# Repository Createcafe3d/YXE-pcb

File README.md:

Big thanks to Rylan @Peachy for opensourcing the entire project.

Peachy Printer was gearing up to manufacture the mini-v1.14 board. If you're wondering what v1.15 is all about, it's a work-in-progress that we started because of a huge panic: right around the time we were getting ready for our final test manufacturing run, the STM32F042 practically vanished from the entire supply chain! We couldn't find them anywhere! So I quickly started redoing the board to use an STM32F070 instead, but in the end the supply chain recovered before we had to pull the trigger on the respin.

**Todos:**
- Create the trans impedence amplifier for the laser sense pin.
  - This lets us tune the laser power to the "draw velocity" - making for nicer cornering and faster printing
  - The sense pin on the laser is currently grounded (and wrongly labeled as "Laser-EN")

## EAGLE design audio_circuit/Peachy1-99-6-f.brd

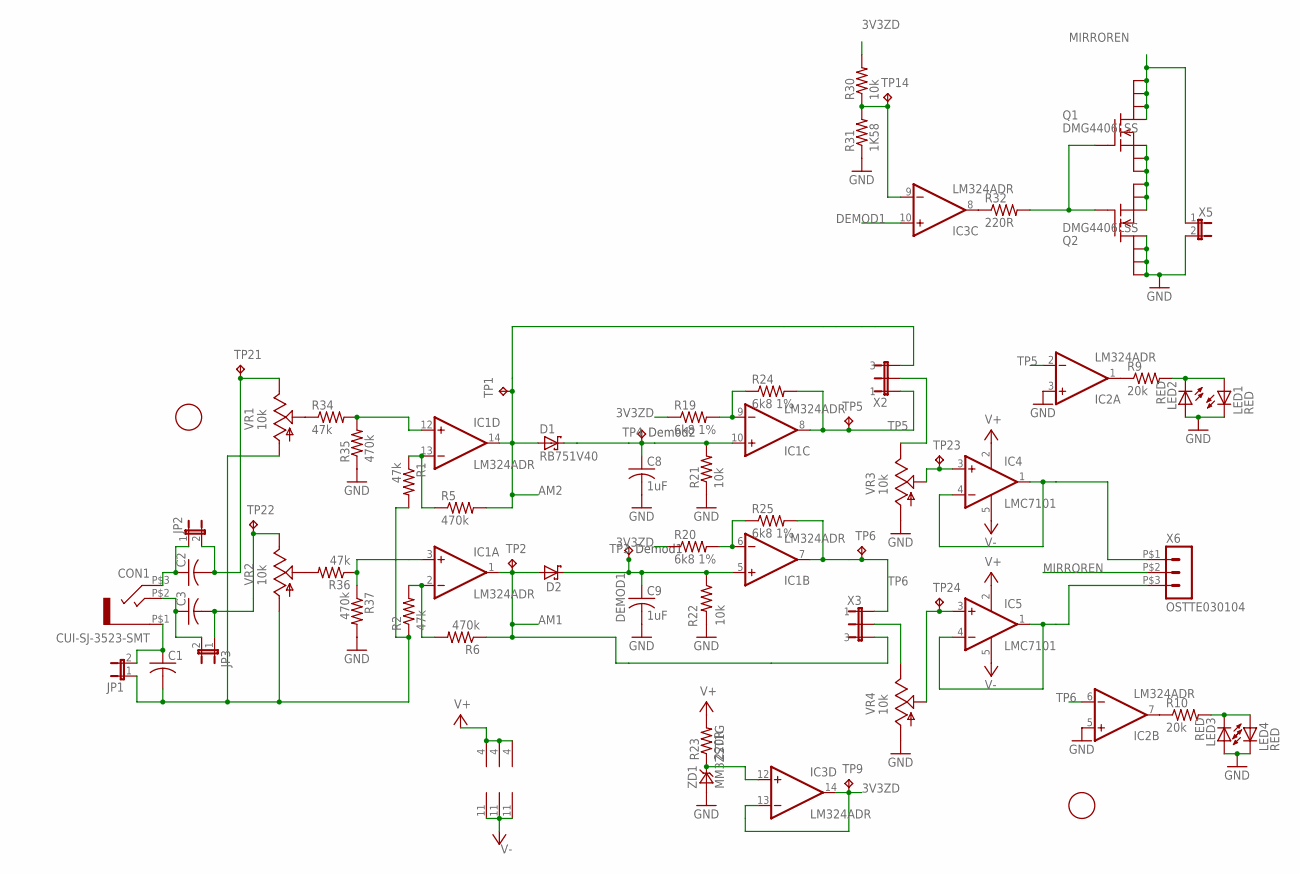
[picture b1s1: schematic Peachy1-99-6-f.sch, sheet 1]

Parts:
C1, C2, C3: C-US0805; C0805
C8, C9: 1uF; C0805; MPN CL21B105KBFNNNE
CON1: CUI-SJ-3523-SMT; MPN SJ-3523-SMT-TR
D1, D2: RB751V40; SOD323-R; MPN RB751V40,115
IC1, IC2, IC3: LM324ADR; SOIC14(TI-PKG-D); MPN LM324ADR
IC4, IC5: LMC7101; SOT23-5; MPN LMC7101BYM5
JP1, JP2, JP3: JUMPER-2SMD-NC; SJ_2S
LED1, LED2, LED3, LED4: RED; CHIPLED_0603; MPN LS L29K-G1J2-1-Z
Q1, Q2: DMG4406LSS; SO8_DMG; MPN DMG4406LSS-13
R1, R2, R34, R36: 47k; R0805; MPN RMCF0805JT47K0; DIGIKEY RMCF0805JT47K0CT-ND
R5, R6, R35, R37: 470k; R0805; MPN RMCF0805JT470K
R9, R10: 20k; R0805; MPN RMCF0805JT20K0
R19, R20, R24, R25: 6k8 1%; R0805; MPN RC0805FR-076K8L
R21, R22, R30: 10k; R0805; MPN RMCF0805JT10K0
R23, R32: 220R; R0805; MPN RMCF0805JT220R
R31: 1K58; R0805; MPN RC0805FR-071K58L
TP1, TP2, TP3, TP4, TP5, TP6, TP9, TP14, TP21, TP22, TP23, TP24: TP017HOLE; TP017TH
U$2, U$3: FIDUCIAL; FIDUCIAL_1MM
VR1, VR2: 10k; 67W; MPN 67WR10KLF
VR3, VR4: 10k; PVZ3A; MPN PVZ3A103C01R00
X2, X3: JUMPER-31-2; SJ_3_PASTE1&2
X5: JUMPER-2SMD-NO; SJ_2S-NO
X6: OSTTE030104; MPN OSTTE030104
ZD1: MM3ZST1G; SOD323-R; MPN BZX384-B3V3,115

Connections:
3V3ZD: IC3.13 (-IN), IC3.14 (OUT), R19.1, R20.1, R30.2, TP9.P$1; also elsewhere on the board
AM1: D2.A, IC1.1 (OUT), R6.1, TP2.P$1, X3.3; also elsewhere on the board
AM2: D1.A, IC1.14 (OUT), R5.2, TP1.P$1, X2.3
DEMOD1: C9.1, D2.C, IC1.5 (+IN), IC3.10 (+IN), R22.1, TP3.P$1
DEMOD2: C8.1, D1.C, IC1.10 (+IN), R21.2, TP4.P$1
GND: C8.2, C9.2, IC2.3 (+IN), IC2.5 (+IN), LED1.C, LED2.A, LED3.A, LED4.C, Q2.P$5 (D), Q2.P$6 (D), Q2.P$7 (D), Q2.P$8 (D), R21.1, R22.2, R31.1, R35.1, R37.2, VR3.P$1 (A), VR4.P$1 (A), X5.2, ZD1.A; also elsewhere on the board
MIRROREN: Q1.P$5 (D), Q1.P$6 (D), Q1.P$7 (D), Q1.P$8 (D), X5.1, X6.P$2 (2)
unnamed: C3.2, JP3.1, TP22.P$1, VR2.E
unnamed: C1.2, JP1.1, R1.2, R2.1, VR1.A, VR2.A
unnamed: R34.1, VR1.S
unnamed: IC1.13 (-IN), R1.1, R5.1
unnamed: IC1.12 (+IN), R34.2, R35.2
unnamed: VR4.P$3 (E), X3.2
unnamed: IC3.12 (+IN), R23.1, ZD1.C
unnamed: IC1.2 (-IN), R2.2, R6.2
unnamed: IC4.3 (+IN), TP23.P$1, VR3.P$2 (S)
unnamed: R36.2, VR2.S
unnamed: IC1.3 (+IN), R36.1, R37.1
unnamed: IC1.9 (-IN), R19.2, R24.1
unnamed: IC2.1 (OUT), R9.1
unnamed: IC1.6 (-IN), R20.2, R25.1
unnamed: IC2.7 (OUT), R10.1
unnamed: IC5.1 (OUT), IC5.4 (-IN), X6.P$3 (3)
unnamed: IC4.1 (OUT), IC4.4 (-IN), X6.P$1 (1)
unnamed: VR3.P$3 (E), X2.2
unnamed: IC5.3 (+IN), TP24.P$1, VR4.P$2 (S)
unnamed: Q1.P$4 (G), Q2.P$4 (G), R32.2
unnamed: Q1.P$1 (S), Q1.P$2 (S), Q1.P$3 (S), Q2.P$1 (S), Q2.P$2 (S), Q2.P$3 (S)
unnamed: IC3.9 (-IN), R30.1, R31.2, TP14.P$1
unnamed: LED1.A, LED2.C, R9.2
unnamed: IC3.8 (OUT), R32.1
unnamed: LED3.C, LED4.A, R10.2
unnamed: C1.1, CON1.P$1 (1), JP1.2
unnamed: C3.1, CON1.P$2 (3), JP3.2
unnamed: C2.1, CON1.P$3 (2), JP2.1
unnamed: C2.2, JP2.2, TP21.P$1, VR1.E
TP5: IC1.8 (OUT), IC2.2 (-IN), R24.2, TP5.P$1, X2.1
TP6: IC1.7 (OUT), IC2.6 (-IN), R25.2, TP6.P$1, X3.1
V+: IC1.4 (V+), IC2.4 (V+), IC3.4 (V+), IC4.2 (V+), IC5.2 (V+), R23.2; also elsewhere on the board
V-: IC1.11 (V-), IC2.11 (V-), IC3.11 (V-), IC4.5 (V-), IC5.5 (V-); also elsewhere on the board

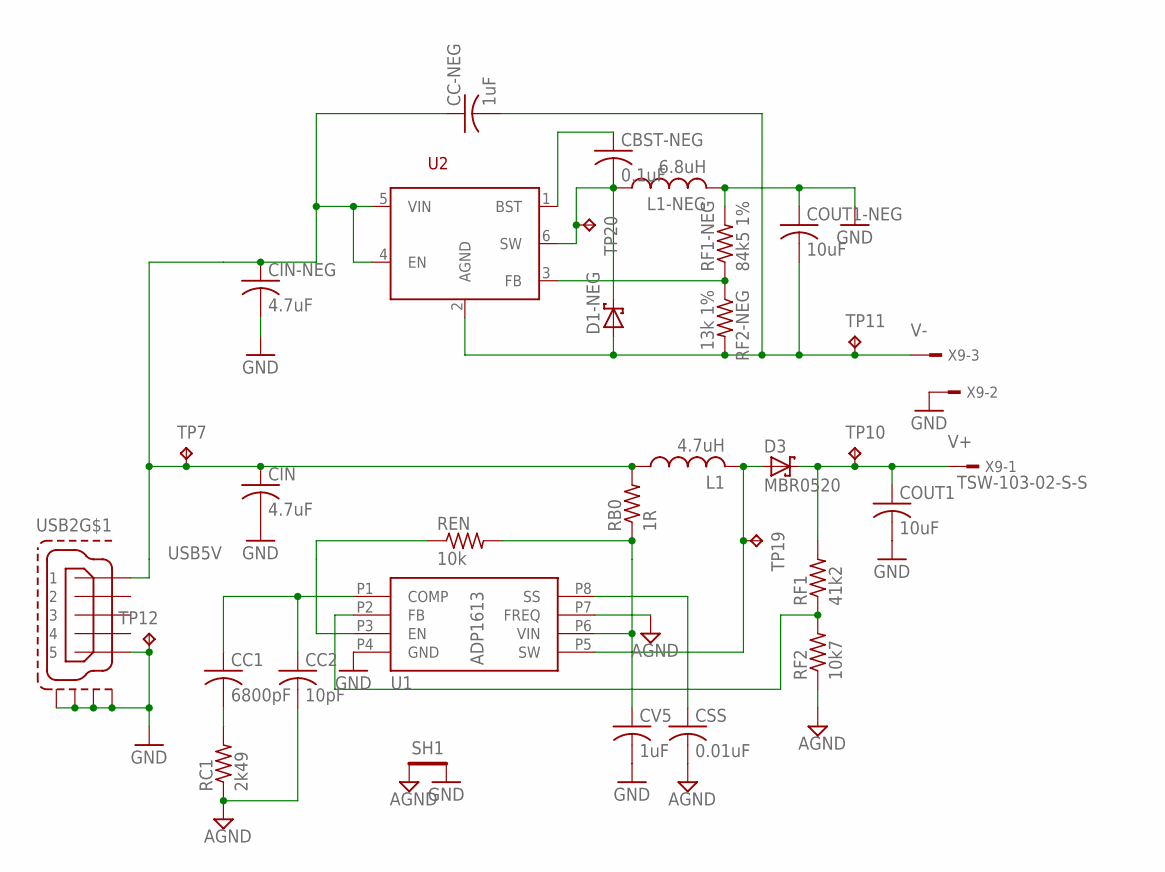
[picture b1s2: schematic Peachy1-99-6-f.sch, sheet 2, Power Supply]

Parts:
CBST-NEG: 0.1uF; C0805; MPN CL21B104KACNNNC
CC1: 6800pF; C0805; MPN CL21B682KBANNNC
CC2: 10pF; C0805; MPN CL21C100JCANNNC
CC-NEG: 1uF; C0805; MPN CL21B105KBFNNNE
CIN: 4.7uF; C0805; MPN CL21A475KOFNNNE
CIN-NEG: 4.7uF; C0805; MPN CL21A475KOFNNNE
COUT1, COUT1-NEG: 10uF; C0805; MPN CL21B106KQQNNNE
CSS: 0.01uF; C0805; MPN CL21B103KBANNNC
CV5: 1uF; C0805; MPN CL21B105KBFNNNE
D1-NEG, D3: MBR0520; SOD123; MPN MBR0520LT3G
L1: 4.7uH; L1210; MPN LQH32PN4R7NN0L
L1-NEG: 6.8uH; L1210; MPN LQH32PN6R8NN0
RB0: 1R; R0805; MPN RMCF0805JT1R00
RC1: 2k49; R0805; MPN RMCF0805FT2K49
REN: 10k; R0805; MPN RMCF0805JT10K0
RF1: 41k2; R0805; MPN RC0805FR-0741K2L
RF1-NEG: 84k5 1%; R0805; MPN RC0805FR-0784K5L
RF2: 10k7; R0805; MPN RC2012F1072CS
RF2-NEG: 13k 1%; R0805; MPN RC0805FR-0713KL
SH1: SHORT-HT5; SHORT_TOP-50
TP7, TP10, TP11, TP12, TP19, TP20: TP017HOLE; TP017TH
U1: ADP1613; RM-8; MPN ADP1613ARMZ-R7
U2: ADP2300; TSOT23-6; MPN ADP2300AUJZ-R7
USB2: FCI-MICROUSBAPCIRCUITS; FCI-USB-10118193-APCIRCUITS; MPN 10118193-0001LF
X9: TSW-103-02-S-S; MPN TSW-103-07-T-S

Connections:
AGND: CC2.2, CSS.2, RC1.1, RF2.1, SH1.1, U1.P7 (FREQ)
BOOST: CBST-NEG.1, U2.1 (BST)
GND: CIN.2, CIN-NEG.2, COUT1.2, COUT1-NEG.1, CV5.2, L1-NEG.2, RF1-NEG.2, SH1.2, TP12.P$1, U1.P4 (GND), USB2.P$5 (5), USB2.P$6 (S1), USB2.P$7 (S2), USB2.P$8 (S3), USB2.P$11 (S4), X9.2; also elsewhere on the board
unnamed: CV5.1, RB0.1, REN.2, U1.P6 (VIN)
unnamed: REN.1, U1.P3 (EN)
unnamed: CSS.1, U1.P8 (SS)
unnamed: RF1.1, RF2.2, U1.P2 (FB)
unnamed: CC1.1, CC2.1, U1.P1 (COMP)
unnamed: CC1.2, RC1.2
unnamed: RF1-NEG.1, RF2-NEG.1, U2.3 (FB)
SW+: D3.A, L1.2, TP19.P$1, U1.P5 (SW)
SW-: CBST-NEG.2, D1-NEG.C, L1-NEG.1, TP20.P$1, U2.6 (SW)
USB5V: CC-NEG.1, CIN.1, CIN-NEG.1, L1.1, RB0.2, TP7.P$1, U2.4 (EN), U2.5 (VIN), USB2.P$1 (1)
V+: COUT1.1, D3.C, RF1.2, TP10.P$1, X9.1; also elsewhere on the board
V-: CC-NEG.2, COUT1-NEG.2, D1-NEG.A, RF2-NEG.2, TP11.P$1, U2.2 (AGND), X9.3; also elsewhere on the board

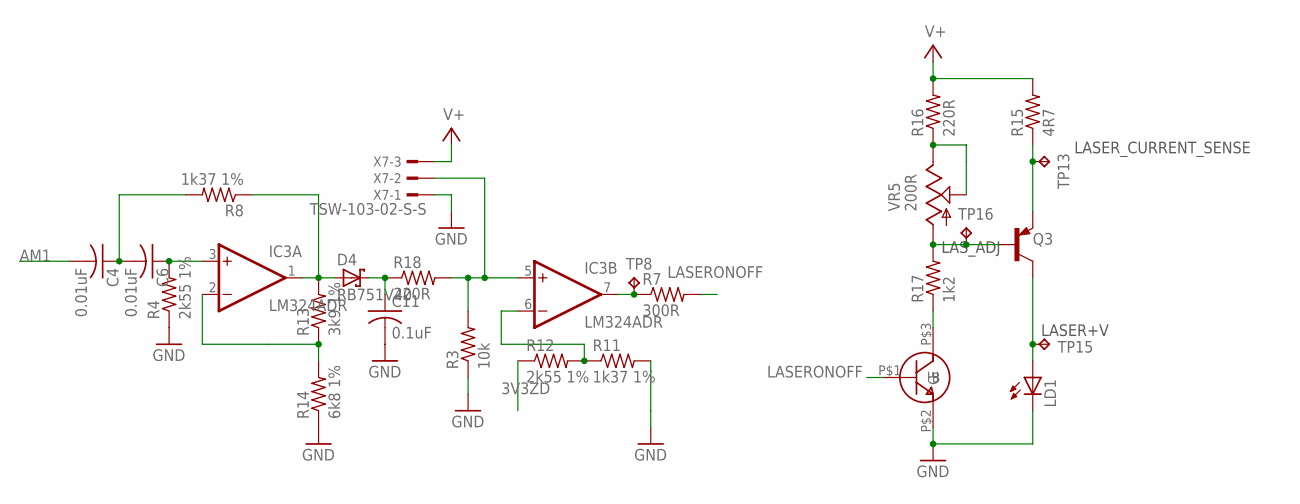
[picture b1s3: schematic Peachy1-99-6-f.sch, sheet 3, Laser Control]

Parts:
C4, C6: 0.01uF; C0805; MPN CL21B103KBANNNC
C11: 0.1uF; C0805; MPN CL21B104KACNNNC
D4: RB751V40; SOD323-R; MPN RB751V40,115
IC3: LM324ADR; SOIC14(TI-PKG-D); MPN LM324ADR
LD1: LASERDIODELD2; LASERDIODE2; MPN 3 x (0552-2-15-15-11-27-10-0)
Q3: BC857CT; SC-75
Q4: MMBT3904; SOT23; MPN MMBT3904,215
R3: 10k; R0805; MPN RMCF0805JT10K0
R4, R12: 2k55 1%; R0805; MPN RC0805FR-072K55L
R7: 300R; R0805; MPN RC0805JR-07300RL
R8, R11: 1k37 1%; R0805; MPN RC0805FR-071K37L
R13: 3k9 1%; R0805; MPN RC0805FR-073K9L
R14: 6k8 1%; R0805; MPN RC0805FR-076K8L
R15: 4R7; R0805; MPN RMCF0805JT4R70
R16, R18: 220R; R0805; MPN RMCF0805JT220R
R17: 1k2; R0805; MPN RC2012J122CS
TP8, TP13, TP15, TP16: TP017HOLE; TP017TH
VR5: 200R; TC33X; MPN ???
X7: TSW-103-02-S-S; MPN TSW-103-07-T-S

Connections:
3V3ZD: R12.1; also elsewhere on the board
AM1: C4.2; also elsewhere on the board
GND: C11.2, LD1.P$3 (C), Q4.P$2 (E), R3.1, R4.1, R11.2, R14.1, X7.1; also elsewhere on the board
LASERONOFF: Q4.P$1 (B), R7.2
unnamed: IC3.5 (+IN), R3.2, R18.2, X7.2
unnamed: IC3.6 (-IN), R11.1, R12.2
unnamed: IC3.2 (-IN), R13.1, R14.2
unnamed: LD1.P$1 (A), Q3.P$3 (C), TP15.P$1
unnamed: IC3.7 (OUT), R7.1, TP8.P$1
unnamed: C6.1, IC3.3 (+IN), R4.2
unnamed: C4.1, C6.2, R8.2
unnamed: D4.A, IC3.1 (OUT), R8.1, R13.2
unnamed: C11.1, D4.C, R18.1
unnamed: R16.1, VR5.P$2 (S), VR5.P$3 (E)
unnamed: Q3.P$1 (B), R17.2, TP16.P$1, VR5.P$1 (A)
unnamed: Q4.P$3 (C), R17.1
unnamed: Q3.P$2 (E), R15.1, TP13.P$1
V+: R15.2, R16.2, X7.3; also elsewhere on the board

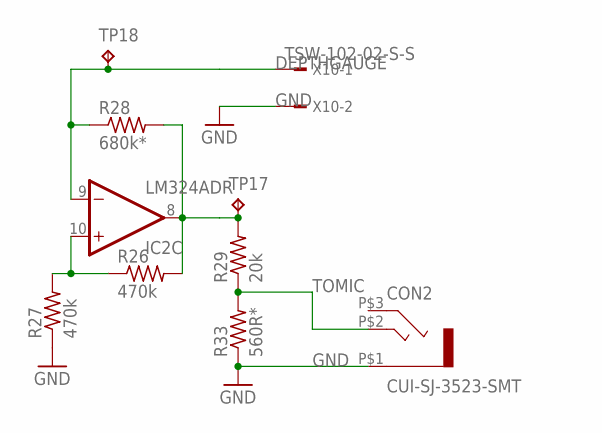
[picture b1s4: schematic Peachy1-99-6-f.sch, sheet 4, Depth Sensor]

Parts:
CON2: CUI-SJ-3523-SMT; MPN SJ-3523-SMT-TR
IC2: LM324ADR; SOIC14(TI-PKG-D); MPN LM324ADR
R26, R27: 470k; R0805; MPN RMCF0805JT470K
R28: 680k*; 70543-02; MPN PPTC021LFBN-RC
R29: 20k; R0805; MPN RMCF0805JT20K0
R33: 560R*; R0805; MPN RMCF0805JT560R
TP17, TP18: TP017HOLE; TP017TH
X10: TSW-102-02-S-S

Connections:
DEPTHGAUGE: IC2.9 (-IN), R28.1, TP18.P$1, X10.1
GND: CON2.P$1 (1), R27.1, R33.1, X10.2; also elsewhere on the board
unnamed: IC2.8 (OUT), R26.2, R28.2, R29.2, TP17.P$1
unnamed: IC2.10 (+IN), R26.1, R27.2
TOMIC: CON2.P$2 (3), R29.1, R33.2

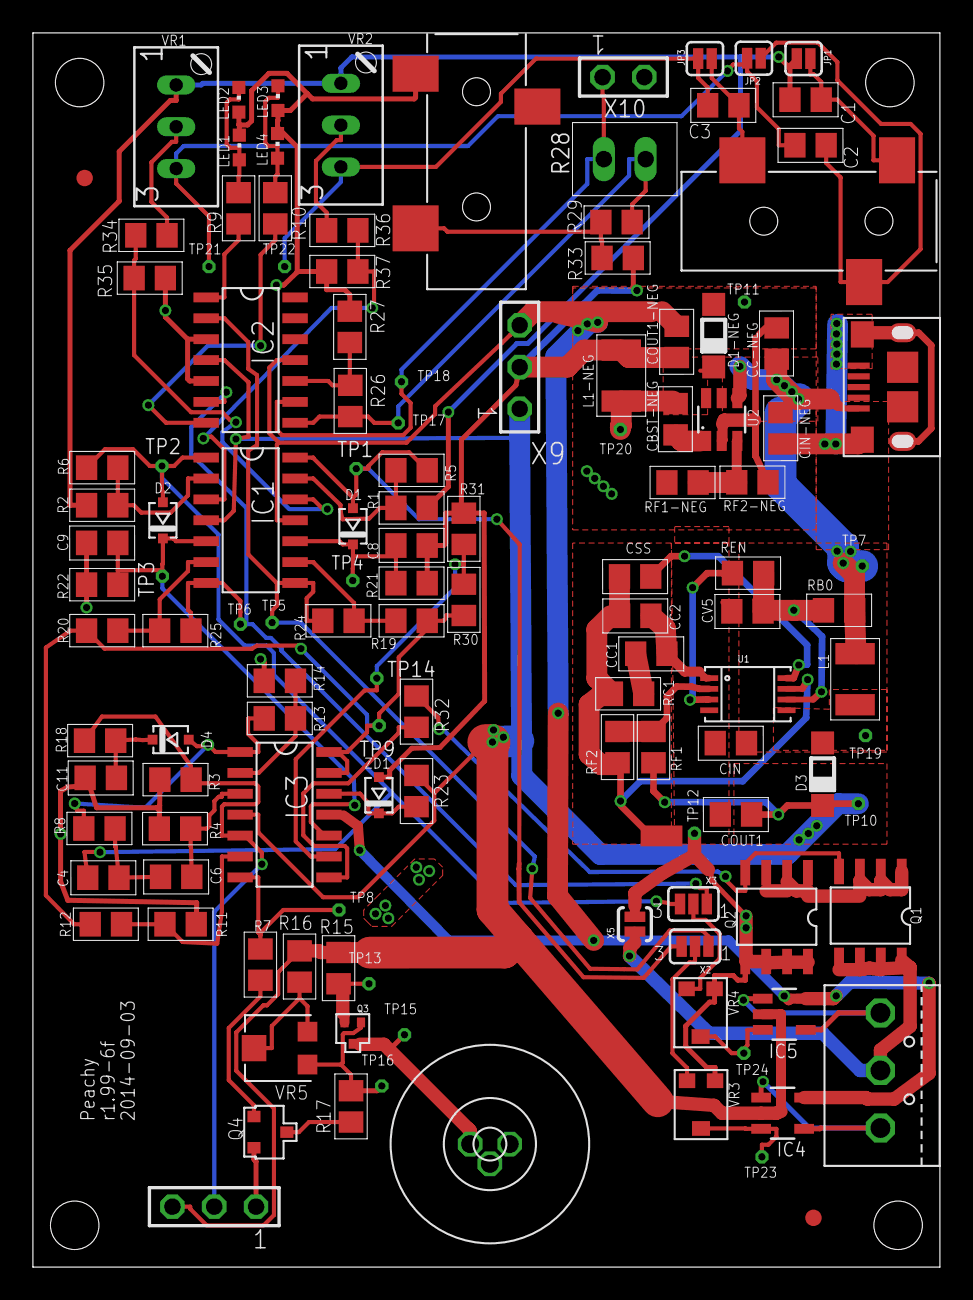
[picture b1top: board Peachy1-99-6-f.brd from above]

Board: 2 copper layers, 55.1 x 75.0 mm, 131 parts (0 on the bottom side), 70 nets.

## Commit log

2016-10-11 Create LICENCE
2016-10-27 Git cleanup, moving old (useless?) files out of the way
2016-10-27 Updated Scotts audio board files with his latest
2016-11-03 More organisation, re-added deleted eagle files -_- woops
2016-11-03 Small README updates
2016-11-03 README Updates Part 2
